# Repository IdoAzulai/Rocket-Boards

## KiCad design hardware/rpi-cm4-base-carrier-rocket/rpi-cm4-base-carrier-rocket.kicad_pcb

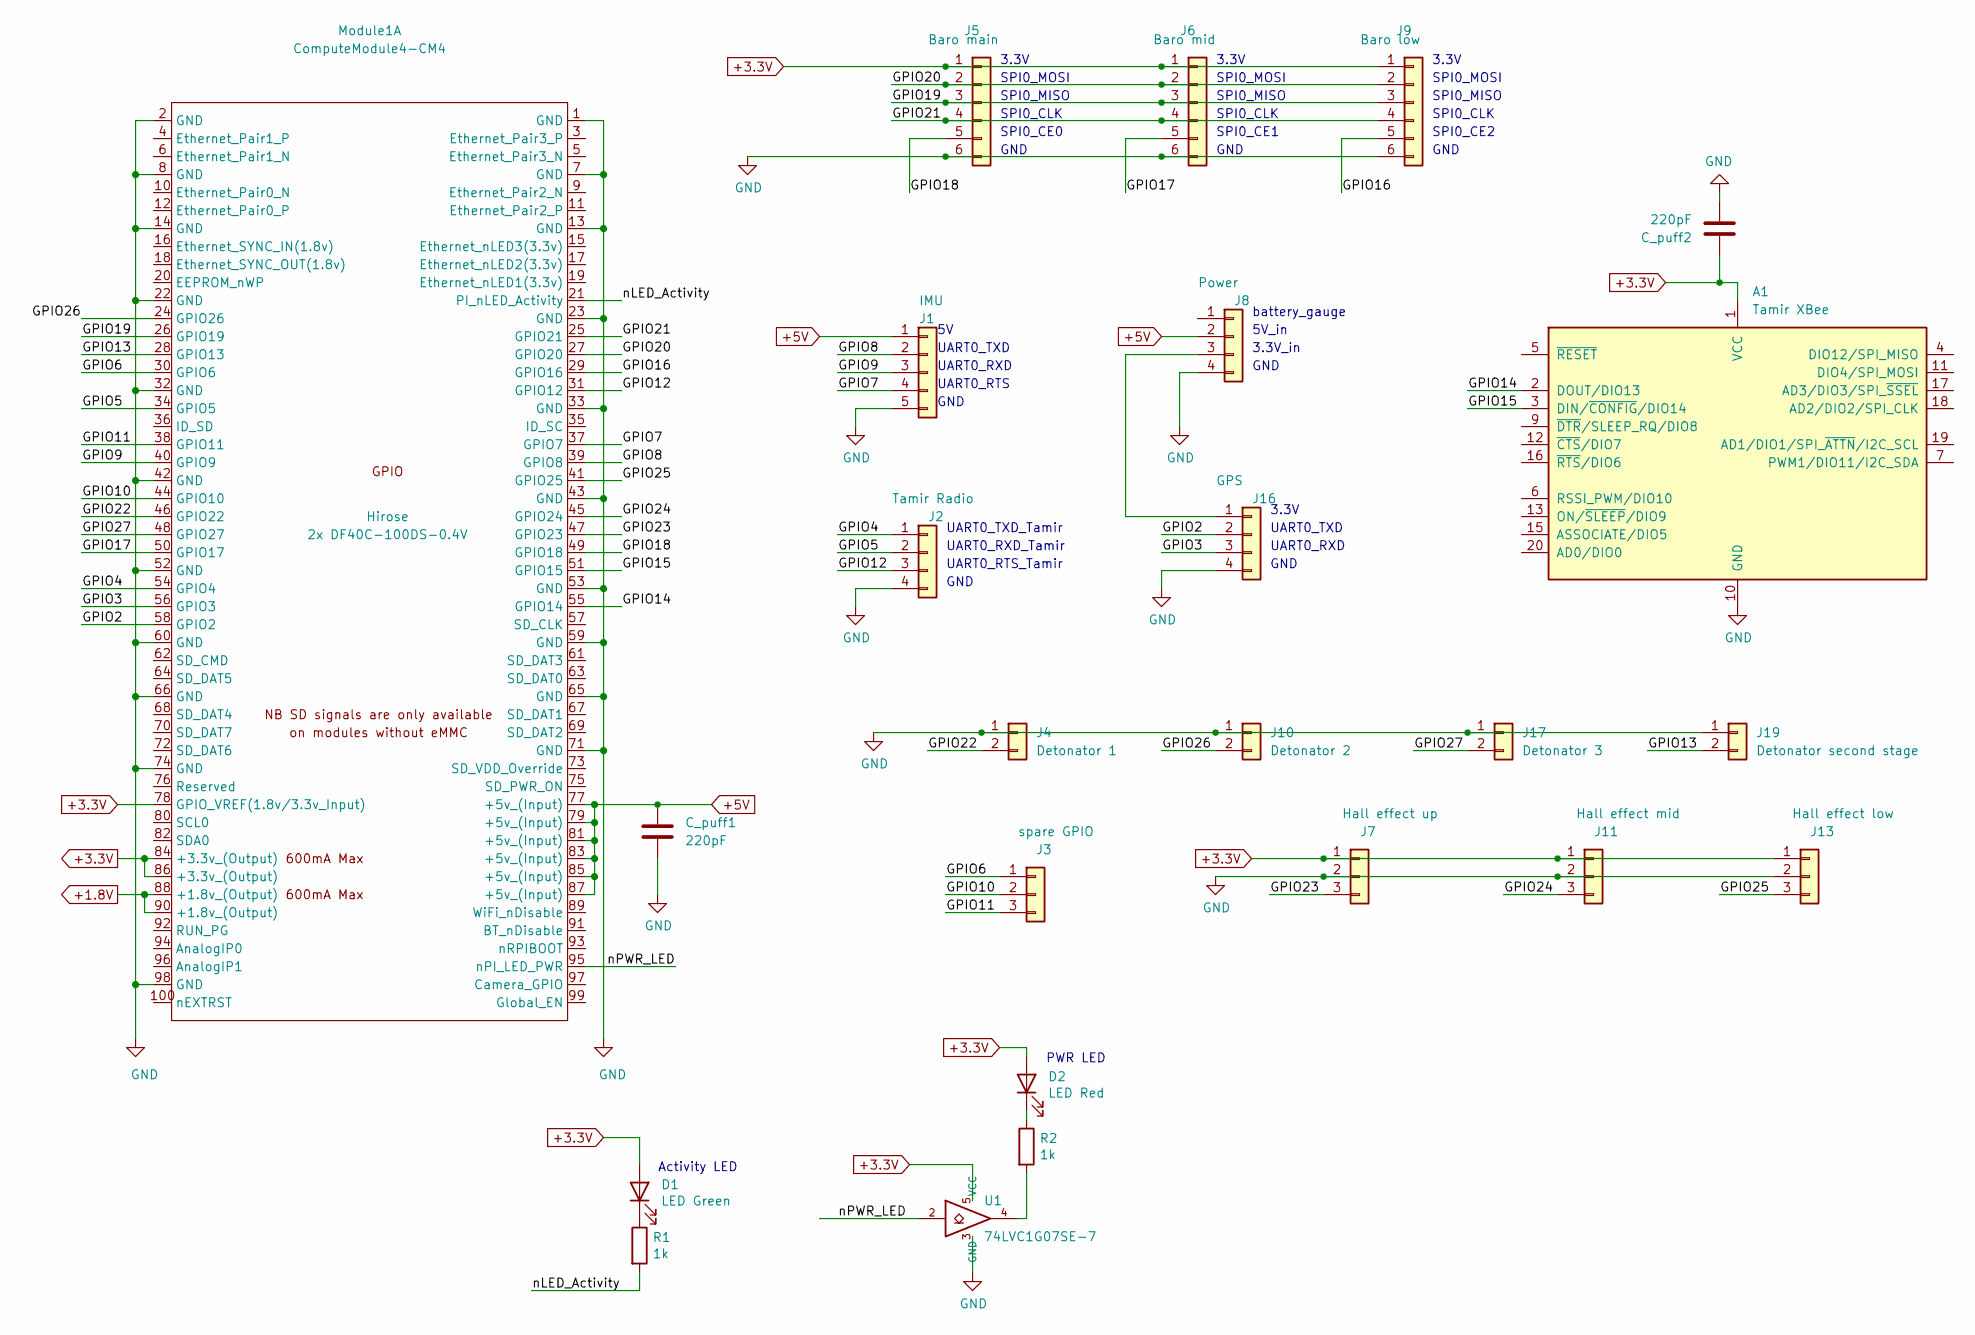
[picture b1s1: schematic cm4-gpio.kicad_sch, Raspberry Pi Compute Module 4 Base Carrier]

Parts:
A1: Tamir XBee; xbee_tht
C_puff1, C_puff2: 220pF; C_0603_1608Metric
D1: LED Green; LED_0603_1608Metric; Part Description Green 572nm LED Indication - Discrete 2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; Digi-Key_PN 160-1478-1-ND
D2: LED Red; LED_0603_1608Metric; Part Description Red 620nm LED Indication - Discrete 2.2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; Digi-Key_PN 160-1479-1-ND
J1: IMU; PinHeader_1x05_P2.54mm_Vertical
J2: Tamir Radio; PinHeader_1x04_P2.54mm_Vertical
J3: spare GPIO; PinHeader_1x03_P2.54mm_Vertical
J4: Detonator 1; PinHeader_1x02_P2.54mm_Vertical
J5: Baro main; PinHeader_1x06_P2.54mm_Vertical
J6: Baro mid; PinHeader_1x06_P2.54mm_Vertical
J7: Hall effect up; PinHeader_1x03_P2.54mm_Vertical
J8: Power; PinHeader_1x04_P2.54mm_Vertical
J9: Baro low; PinHeader_1x06_P2.54mm_Vertical
J10: Detonator 2; PinHeader_1x02_P2.54mm_Vertical
J11: Hall effect mid; PinHeader_1x03_P2.54mm_Vertical
J13: Hall effect low; PinHeader_1x03_P2.54mm_Vertical
J16: GPS; PinHeader_1x04_P2.54mm_Vertical
J17: Detonator 3; PinHeader_1x02_P2.54mm_Vertical
J19: Detonator second stage; PinHeader_1x02_P2.54mm_Vertical
Module1: ComputeModule4-CM4; Raspberry-Pi-4-Compute-Module; MPN 2x DF40C-100DS-0.4V; Digi-Key_PN 2x H11615CT-ND
R1, R2: 1k; R_0603_1608Metric_Pad0.98x0.95mm_HandSolder; MPN RC0603FR-071KL; Digi-Key_PN 311-1.00KHRCT-ND
U1: 74LVC1G07SE-7; SOT-353_SC-70-5; Part Description Buffer, Non-Inverting 1 Element 1 Bit p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; Digi-Key_PN 74LVC1G07SE-7DICT-ND

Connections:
+1.8V: Module1.88 (+1.8v_(Output)), Module1.90 (+1.8v_(Output))
+3.3V: A1.1 (VCC), C_puff2.1, D1.2 (A), D2.2 (A), J5.1, J6.1, J7.1, J9.1, J11.1, J13.1, Module1.78 (GPIO_VREF(1.8v/3.3v_Input)), Module1.84 (+3.3v_(Output)), Module1.86 (+3.3v_(Output)), U1.5 (VCC); also elsewhere on the board
+5V: C_puff1.1, J1.1, J8.2, Module1.77 (+5v_(Input)), Module1.79 (+5v_(Input)), Module1.81 (+5v_(Input)), Module1.83 (+5v_(Input)), Module1.85 (+5v_(Input)), Module1.87 (+5v_(Input)); also elsewhere on the board
/CM4 GPIO/GPIO2: J16.2, Module1.58 (GPIO2)
/CM4 GPIO/GPIO3: J16.3, Module1.56 (GPIO3)
/CM4 GPIO/GPIO4: J2.1, Module1.54 (GPIO4)
/CM4 GPIO/GPIO5: J2.2, Module1.34 (GPIO5)
/CM4 GPIO/GPIO6: J3.1, Module1.30 (GPIO6)
/CM4 GPIO/GPIO7: J1.4, Module1.37 (GPIO7)
/CM4 GPIO/GPIO8: J1.2, Module1.39 (GPIO8)
/CM4 GPIO/GPIO9: J1.3, Module1.40 (GPIO9)
/CM4 GPIO/GPIO10: J3.2, Module1.44 (GPIO10)
/CM4 GPIO/GPIO11: J3.3, Module1.38 (GPIO11)
/CM4 GPIO/GPIO12: J2.3, Module1.31 (GPIO12)
/CM4 GPIO/GPIO13: J19.2, Module1.28 (GPIO13)
/CM4 GPIO/GPIO14: A1.2 (DOUT/DIO13), Module1.55 (GPIO14)
/CM4 GPIO/GPIO15: A1.3 (DIN/~CONFIG/DIO14), Module1.51 (GPIO15)
/CM4 GPIO/GPIO16: J9.5, Module1.29 (GPIO16)
/CM4 GPIO/GPIO17: J6.5, Module1.50 (GPIO17)
/CM4 GPIO/GPIO18: J5.5, Module1.49 (GPIO18)
/CM4 GPIO/GPIO19: J5.3, J6.3, J9.3, Module1.26 (GPIO19)
/CM4 GPIO/GPIO20: J5.2, J6.2, J9.2, Module1.27 (GPIO20)
/CM4 GPIO/GPIO21: J5.4, J6.4, J9.4, Module1.25 (GPIO21)
/CM4 GPIO/GPIO22: J4.2, Module1.46 (GPIO22)
/CM4 GPIO/GPIO23: J7.3, Module1.47 (GPIO23)
/CM4 GPIO/GPIO24: J11.3, Module1.45 (GPIO24)
/CM4 GPIO/GPIO25: J13.3, Module1.41 (GPIO25)
/CM4 GPIO/GPIO26: J10.2, Module1.24 (GPIO26)
/CM4 GPIO/GPIO27: J17.2, Module1.48 (GPIO27)
/CM4 GPIO/nLED_Activity: Module1.21 (PI_nLED_Activity), R1.2
/CM4 GPIO/nPWR_LED: Module1.95 (nPI_LED_PWR), U1.2
GND: A1.10 (GND), C_puff1.2, C_puff2.2, J1.5, J2.4, J4.1, J5.6, J6.6, J7.2, J8.4, J9.6, J10.1, J11.2, J13.2, J16.4, J17.1, J19.1, Module1.1 (GND), Module1.2 (GND), Module1.7 (GND), Module1.8 (GND), Module1.13 (GND), Module1.14 (GND), Module1.22 (GND), Module1.23 (GND), Module1.32 (GND), Module1.33 (GND), Module1.42 (GND), Module1.43 (GND), Module1.52 (GND), Module1.53 (GND), Module1.59 (GND), Module1.60 (GND), Module1.65 (GND), Module1.66 (GND), Module1.71 (GND), Module1.74 (GND), Module1.98 (GND), Module1.107 (GND), Module1.108 (GND), Module1.113 (GND), Module1.114 (GND), Module1.119 (GND), Module1.120 (GND), Module1.125 (GND), Module1.126 (GND), Module1.131 (GND), Module1.132 (GND), Module1.137 (GND), Module1.138 (GND), Module1.144 (GND), Module1.150 (GND), Module1.155 (GND), Module1.156 (GND), Module1.161 (GND), Module1.162 (GND), Module1.167 (GND), Module1.168 (GND), Module1.173 (GND), Module1.174 (GND), Module1.179 (GND), Module1.180 (GND), Module1.185 (GND), Module1.186 (GND), Module1.191 (GND), Module1.192 (GND), Module1.197 (GND), Module1.198 (GND), U1.3 (GND); also elsewhere on the board
unnamed: D1.1 (K), R1.1
unnamed: D2.1 (K), R2.1
unnamed: J8.3, J16.1
unnamed: R2.2, U1.4

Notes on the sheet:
SPI0_CLK
SPI0_MOSI
GND
3.3V_in
SPI0_MISO
SPI0_CE2
battery_gauge
UART0_TXD
UART0_RTS
UART0_RXD
3.3V
UART0_RXD_Tamir
SPI0_CE1
UART0_TXD_Tamir
SPI0_CE0
Activity LED
5V_in
UART0_RTS_Tamir
PWR LED

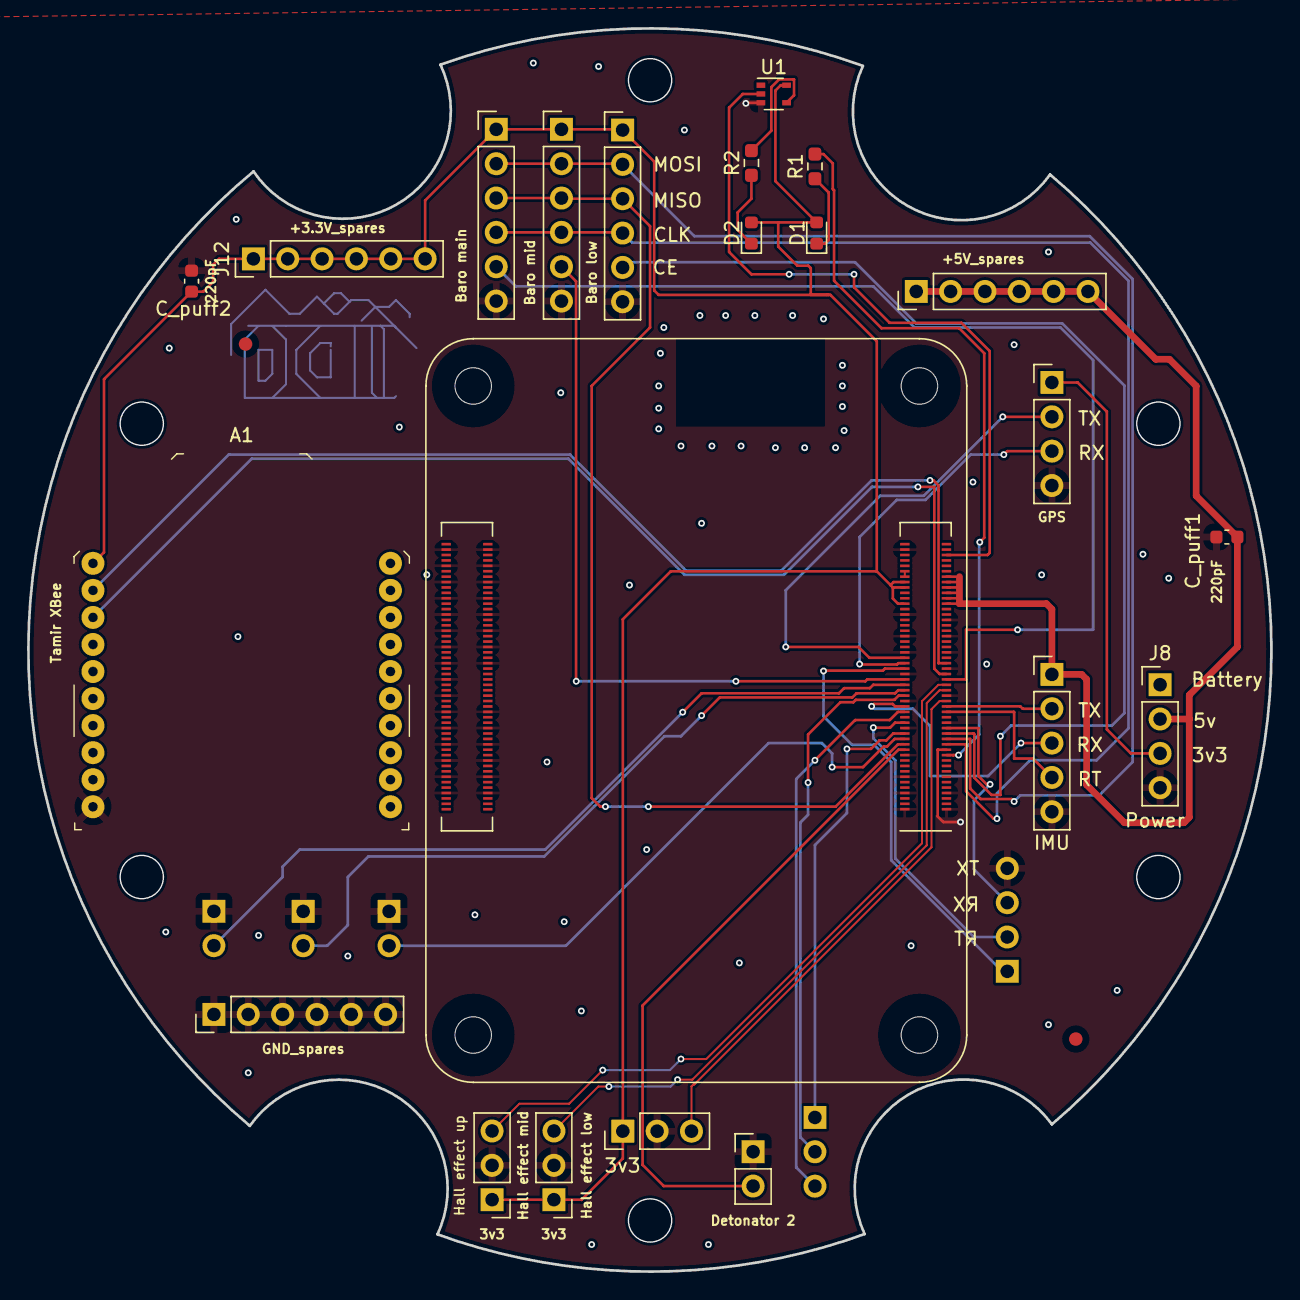
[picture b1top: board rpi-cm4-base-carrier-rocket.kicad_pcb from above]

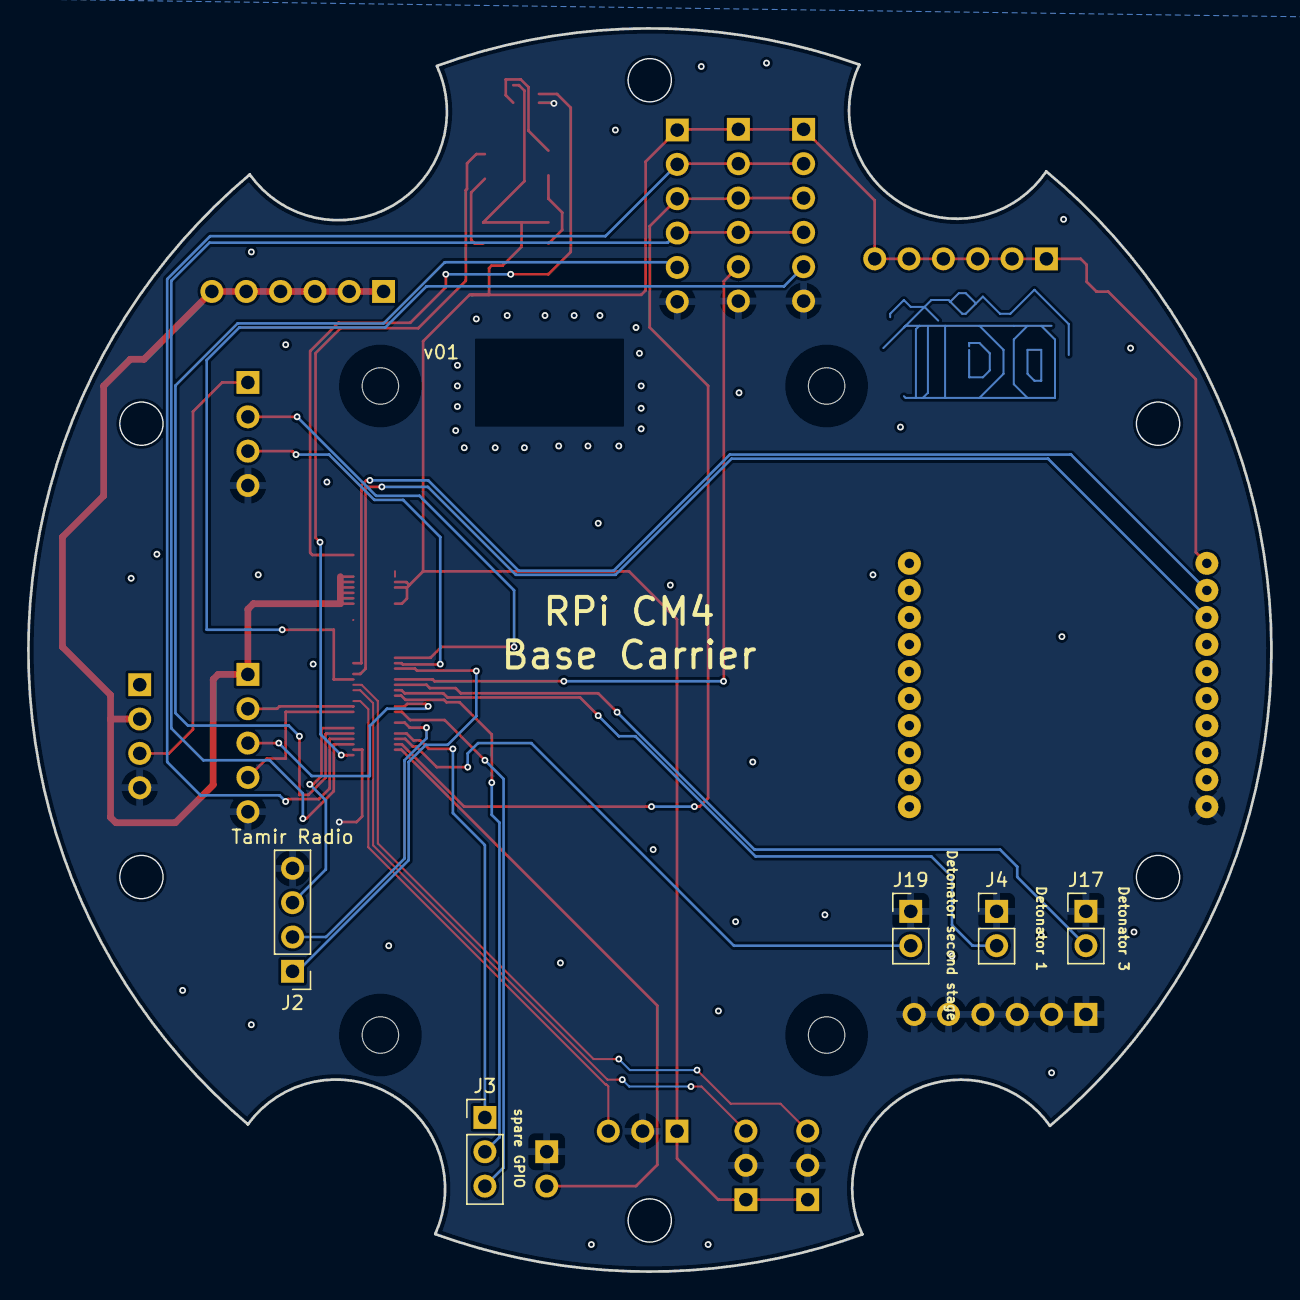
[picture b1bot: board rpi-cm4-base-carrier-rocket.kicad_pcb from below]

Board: 2 copper layers, 91.9 x 91.9 mm, 27 parts (5 on the bottom side), 36 nets.

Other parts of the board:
J12: +3.3V_spares; PinHeader_1x06_P2.54mm_Vertical
J14: +5V_spares; PinHeader_1x06_P2.54mm_Vertical
J15: GND_spares; PinHeader_1x06_P2.54mm_Vertical

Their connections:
+3.3V: J12.1, J12.2, J12.3, J12.4, J12.5, J12.6; also elsewhere on the board
+5V: J14.1, J14.2, J14.3, J14.4, J14.5, J14.6; also elsewhere on the board
GND: J15.1, J15.2, J15.3, J15.4, J15.5, J15.6; also elsewhere on the board

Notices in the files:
hardware/rpi-cm4-base-carrier-rocket/cm4-gpio.kicad_sch:
creativecommons.org/licenses/by-sa/4.0
License: CC BY 4.0
